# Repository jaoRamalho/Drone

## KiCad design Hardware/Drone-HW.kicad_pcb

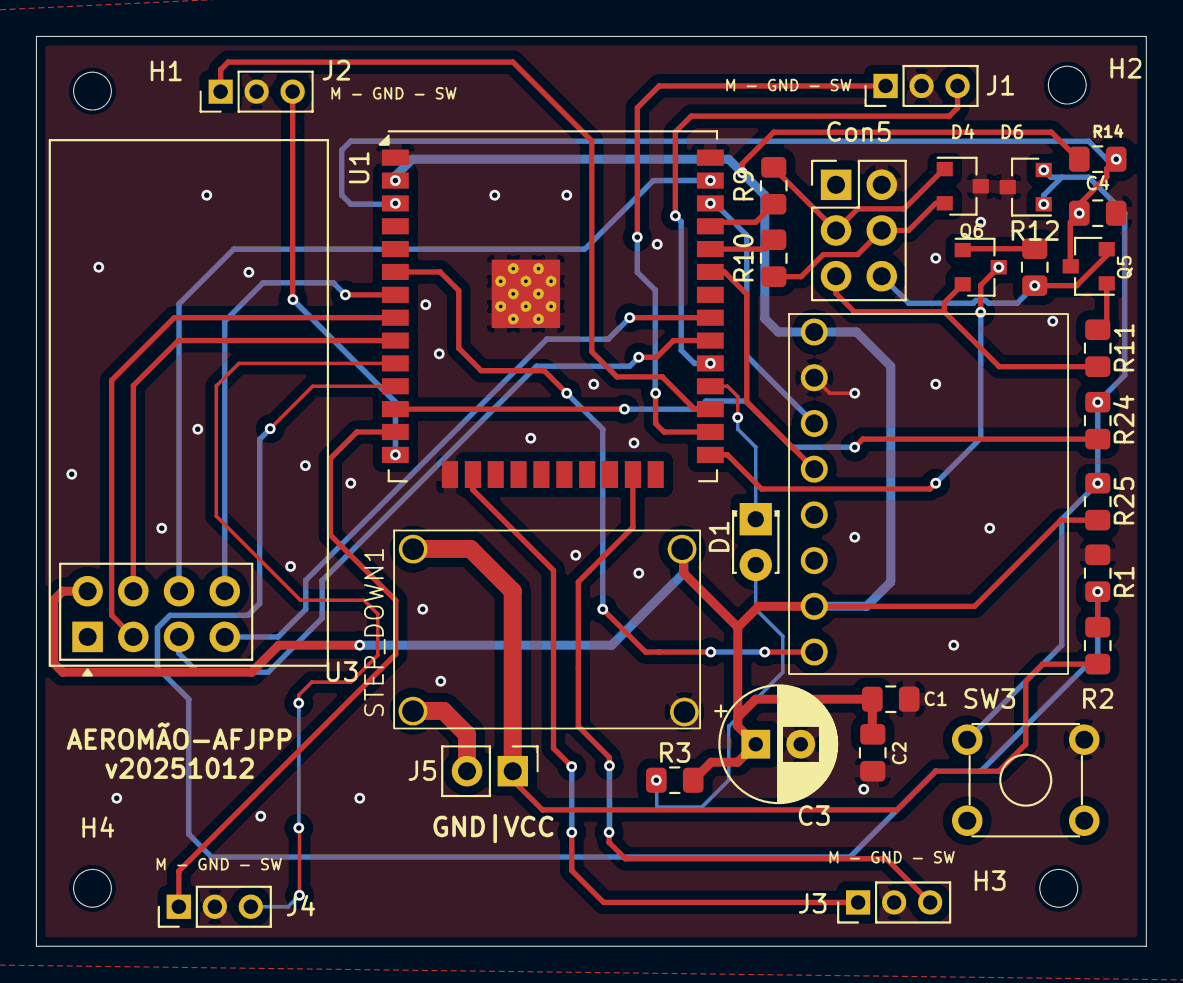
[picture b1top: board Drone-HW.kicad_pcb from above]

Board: 2 copper layers, 61.7 x 50.5 mm, 34 parts (0 on the bottom side), 36 nets.

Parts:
C1, C2: 10uF/25V; C_0805_2012Metric_Pad1.15x1.40mm_HandSolder
C3: 220uF/16V; CP_Radial_D6.3mm_P2.50mm
C4: 100nF/50V; C_0805_2012Metric_Pad1.15x1.40mm_HandSolder
Con5: espTool_conn; PinHeader_2x03_P2.54mm_Vertical
D1: LED; LED_D1.8mm_W3.3mm_H2.4mm
D4, D6: TVS 3,3V; SOT-23
H1, H2, H3, H4: MountingHole; MountingHole_2.1mm
J1, J2, J3, J4: Conn_01x03; PinHeader_1x03_P2.00mm_Vertical
J5: Conn_01x02_Pin; PinHeader_1x02_P2.54mm_Vertical
Q5, Q6: BC846; SOT-23
R1, R14, R25: 10k; R_0805_2012Metric_Pad1.15x1.40mm_HandSolder
R2: 15k; R_0805_2012Metric_Pad1.15x1.40mm_HandSolder
R3: 470R; R_0805_2012Metric_Pad1.15x1.40mm_HandSolder
R9, R10, R24: 49,9R; R_0805_2012Metric_Pad1.15x1.40mm_HandSolder
R11, R12: 4,7k; R_0805_2012Metric_Pad1.15x1.40mm_HandSolder
STEP_DOWN1: STEPDOWN_23V_3V3; StepDown3v3_Module
SW3: Tactile; SW_TH_Tactile_Omron_B3F-10xx
U1: ESP32-WROOM-32D; ESP32-WROOM-32U
U2: U2; MPU6050_Module
U3: NRF24L01_Breakout; nRF24L01_Breakout

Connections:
+3V3: C1.1, C2.1, C3.1, R3.1, R14.1, R25.1, STEP_DOWN1.3 (+OUT), U1.2 (VDD), U2.1 (VCC), U2.7 (ADO), U3.2 (VCC)
+7V4: J5.1, R2.1, STEP_DOWN1.1 (+IN)
/B_START: R24.1, U1.12 (IO27)
/CE: U1.8 (IO32), U3.3 (CE)
/DTR_ESP: Con5.5 (DTR), Q6.2 (E), R11.2
/EN_ESP: C4.1, Q5.3 (C), R14.2, U1.3 (EN)
/INT: U1.6 (IO34_(IN)), U2.8 (INT)
/IO0_ESP: Q6.3 (C), U1.25 (IO0(SPU))
/IRQ: U1.7 (IO35_(IN)), U3.8 (IRQ)
/MISO: U1.31 (IO19), U3.7 (MISO)
/MOSI: U1.37 (IO23), U3.6 (MOSI)
/Motor1: J1.1, U1.26 (IO4)
/Motor2: J2.1, U1.27 (IO16)
/Motor3: J3.1, U1.16 (IO13)
/Motor4: J4.1, U1.13 (IO14)
/RTS_ESP: Con5.6 (RTS), Q5.2 (E), R12.2
/RX_USB: R10.2, U1.34 (RXD0/IO3)
/SCK: U1.30 (IO18), U3.5 (SCK)
/SCL-SPU: U1.36 (IO22), U2.3 (SCL)
/SDA-SPU: U1.33 (IO21), U2.4 (SDA)
/TX_USB: R9.1, U1.35 (TXD0/IO1)
/V_Bat: R1.1, R2.2, U1.11 (IO26)
/sw1: J1.3, U1.29 (IO5(SPU))
/sw2: J2.3, U1.14 (IO12(SPD))
/sw3: J3.3, U1.23 (IO15(SPU))
/sw4: J4.3, U1.10 (IO25)
/~CSN: U1.9 (IO33), U3.4 (~CSN)
GND: C1.2, C2.2, C3.2, C4.2, Con5.2 (GND), D4.3 (A1), D6.3 (A1), J1.2, J2.2, J3.2, J4.2, R1.2, STEP_DOWN1.4 (-OUT), SW3.2, U1.1 (GND), U1.15 (GND), U1.38 (GND), U1.39 (PAD), U2.2 (GND), U3.1 (GND)
GND_7V4: J5.2, STEP_DOWN1.2 (-IN)
unnamed: Con5.4 (RX), D4.2 (A2), R10.1
unnamed: Con5.3 (TX), D4.1 (common), R9.2
unnamed: D1.2 (A), R3.2
unnamed: D1.1 (K), U1.28 (IO17)
unnamed: D6.1 (common), D6.2 (A2), R24.2, R25.2, SW3.1
unnamed: Q5.1 (B), R11.1
unnamed: Q6.1 (B), R12.1

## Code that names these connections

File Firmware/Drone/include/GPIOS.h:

#ifndef GPIOS_H
#define GPIOS_H

#include "stdint.h"

// LED de status
static const uint8_t LED = 17; 

// Botão start
static const uint8_t PIN_BUTTON = 27;


static const uint8_t PIN_I00_ESP = 0; // GPIO0

// Motores
static const uint8_t PIN_M1 = 4;
static const uint8_t PIN_M2 = 16;
static const uint8_t PIN_M3 = 13;
static const uint8_t PIN_M4 = 14;

// I2C
static const uint8_t PIN_SCK = 18;
static const uint8_t PIN_MISO = 19;
static const uint8_t PIN_SDA = 21;
static const uint8_t PIN_SCL = 22;
static const uint8_t PIN_MOSI = 23;

// Comunicação (se forem usados)
static const uint8_t PIN_TX_USB = 1;
static const uint8_t PIN_RX_USB = 3;

// Outros sinais (se usados para módulo RF ou sensores)
static const uint8_t PIN_CE  = 32;
static const uint8_t PIN_CSN = 33;
static const uint8_t PIN_IRQ = 35;

static const uint8_t INT_GYRO_PIN = 34; // GPIO de interrupção do giroscópio

static const uint8_t V_BAT_PIN = 26; // GPIO para leitura da tensão da bateria

#endif // GPIOS_H

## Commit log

2025-08-13 Iniciando rep
2025-08-17 Hardware iniciado, modulo MPU6050, controle motores, ESP e gravacçao prontos
2025-08-17 Adicionando projeto de firmware
2025-08-26 Adicionando sybols e footprint dos escs e symbol do stepdown
2025-09-04 hardware arrumado, retirando escs da pcb e diminuindo tamanho
2025-09-06 Retirando modulos escs da pcb
2025-09-06 Iniciando firmware, configuracao do pwm e Gyroscopios feitas, falta os testes
2025-09-06 Adicionando delay na inicializacao do giroscopio
2025-09-07 Atualização dos pinos GPIO e configuração do .gitignore
    - Atualizados os pinos dos motores e outros periféricos no GPIOS.h
    - Adicionado .gitignore para ignorar arquivos do VS Code, PlatformIO e temporários
2025-09-07 Melhoria no .gitignore para evitar modificações indesejadas do KiCad
    - Adicionados mais arquivos temporários e de backup do KiCad
    - Inclui arquivos .kicad_sch.lck para evitar modificações automáticas
2025-09-10 Arruamndo classe de gyroscopio e adicionando arquivos de interrupcoes
2025-09-11 Iniciando controlador
2025-09-12 Finalizando hardware aguardando revisão
2025-09-16 Adicionando arquitetura de controle
2025-09-20 commitando teste
2025-09-20 Transformando pwm para interrupção padrão
2025-09-21 Implementação completa da comunicação RF24 como singleton
    - Adicionada classe Communication como singleton para RF24
    - Implementada comunicação bidirecional com ACK payload
    - Configurado VS Code para desenvolvimento ESP32/PlatformIO
    - Atualizados GPIOs para nova configuração
    - Adicionadas configurações de timer para pings automáticos
    Funcionalidades:
2025-10-01 Arrumando hardware
2025-10-01 Arrumando erros de DRC hw
2025-10-02 alteracoes finais
2025-10-05 State para ativação do motor funcionando, falta criar discretização de aceleração
2025-10-14 Adicionando arquivos de timers e Melhorando maquina de estados para controle de motores
2025-10-14 Dando push na versão final de hardware
2025-10-14 Removendo arquivo de controle de pwm, usando lib externa
2025-10-14 arrumando .gitignore
2025-10-26 Comunicação por rádio funcional com ping por interrupção e em classe Própria, interrupção agora no arquivo Timer também
2025-10-26 Comunicação por rádio funcional com protocolo simples que verifica se algum bit foi corrompido por checksum com XOR e tenta mandar o mesmo comando até 3 vezes se não foi enviado e recebido
2025-10-28 Software da câmera + comunicação com a esp
2025-10-29 Ultimas alteracoes feitas em aula
2025-10-31 Firmware separado em controle e drone
2025-11-03 Pousos automáticos em situação de perda de conexão ou bateria baixa
2025-11-05 Comunicação funcionando com dois esp32 e em pastas separadas no firmware
2025-11-05 v3.2 Formatando codigo e arquivos
2025-11-10 Incluindo led e separando melhor as funcoes do Control
2025-11-10 Arrumando cases parte 1
2025-11-11 adicionado LABEL para os sinais
2025-11-11 Teste de hardware
2025-11-11 Alterando comentarios de logs para melhorar restreabilidade de erros
2025-11-12 Adicionando funcoes para controle dos motores
2025-11-12 implementado novos gestos
2025-11-12 Latencia e enums
2025-11-18 Teste de latencia feito
2025-11-19 Adicionando controle por interrupcao de botao
2025-11-20 Adicionando leitura de bateria, junto com funcoes get para retorno
2025-11-23 Pequenos ajustes na Comunicação
2025-11-24 Setagem dos setpoints para o futuro pid
2025-11-29 Adicionando alteracoes da aula
2025-12-03 Adicionando alteracoes parciais
2025-12-04 Correção nos Id's dos gestos, deixando somente os comandos que realmente serão utilizados
2025-12-10 Adicionando mudancas de pid
2025-12-14 Adicionando alteracoes de pid
2025-12-14 Arrumei a parte da comunicação que estava errada
2025-12-15 Adicionando alteracoes finais de integração
2025-12-16 Adicionando alteracoes
2025-12-16 Arrumando duplicada de controle
2025-12-17 Versão funcional depois da apresentacao 5
2025-12-17 Vesão funcional depois do entregavel 5
